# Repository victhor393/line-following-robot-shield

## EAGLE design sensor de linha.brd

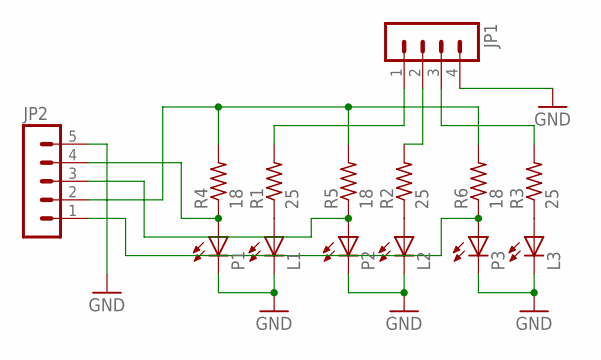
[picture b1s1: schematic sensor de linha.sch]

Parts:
JP1: MA04-1
JP2: MA05-1
L1, L2, L3: LED3MM
P1, P2, P3: LED3MM
R1, R2, R3: 25; R0805
R4, R5, R6: 18; R0805

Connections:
GND: JP1.4, JP2.5, L1.K (C), L2.K (C), L3.K (C), P1.K (C), P2.K (C), P3.K (C)
unnamed: JP1.1, R1.2
unnamed: L1.A, R1.1
unnamed: JP1.2, R2.2
unnamed: JP1.3, R3.2
unnamed: L2.A, R2.1
unnamed: L3.A, R3.1
unnamed: JP2.4, P1.A, R4.1
unnamed: JP2.1, P3.A, R6.1
unnamed: JP2.2, R4.2, R5.2, R6.2
unnamed: JP2.3, P2.A, R5.1

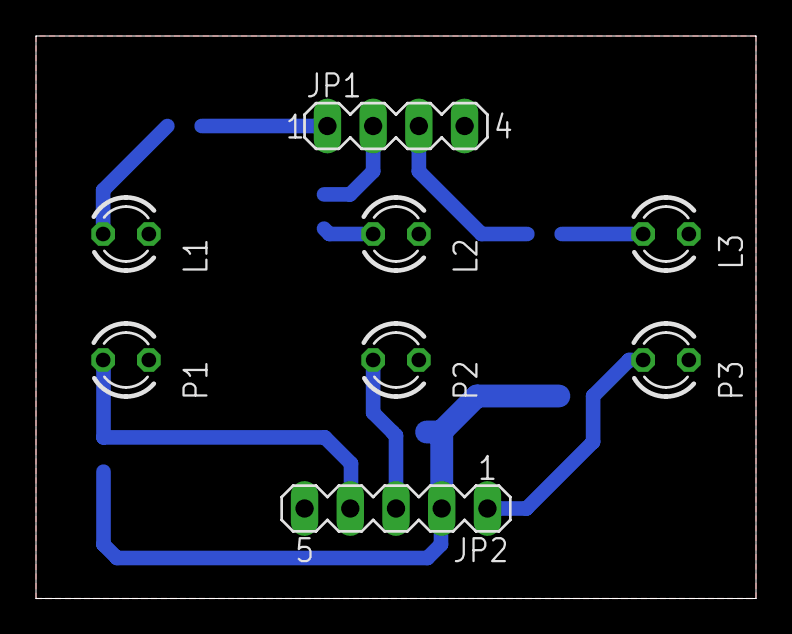
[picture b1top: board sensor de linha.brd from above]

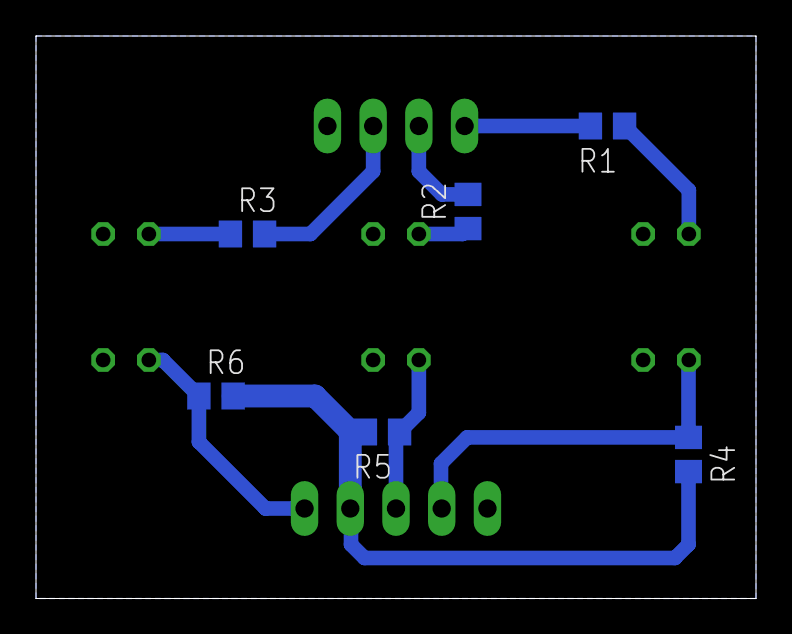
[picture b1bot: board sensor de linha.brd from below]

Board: 2 copper layers, 40.0 x 31.2 mm, 14 parts (6 on the bottom side), 11 nets.

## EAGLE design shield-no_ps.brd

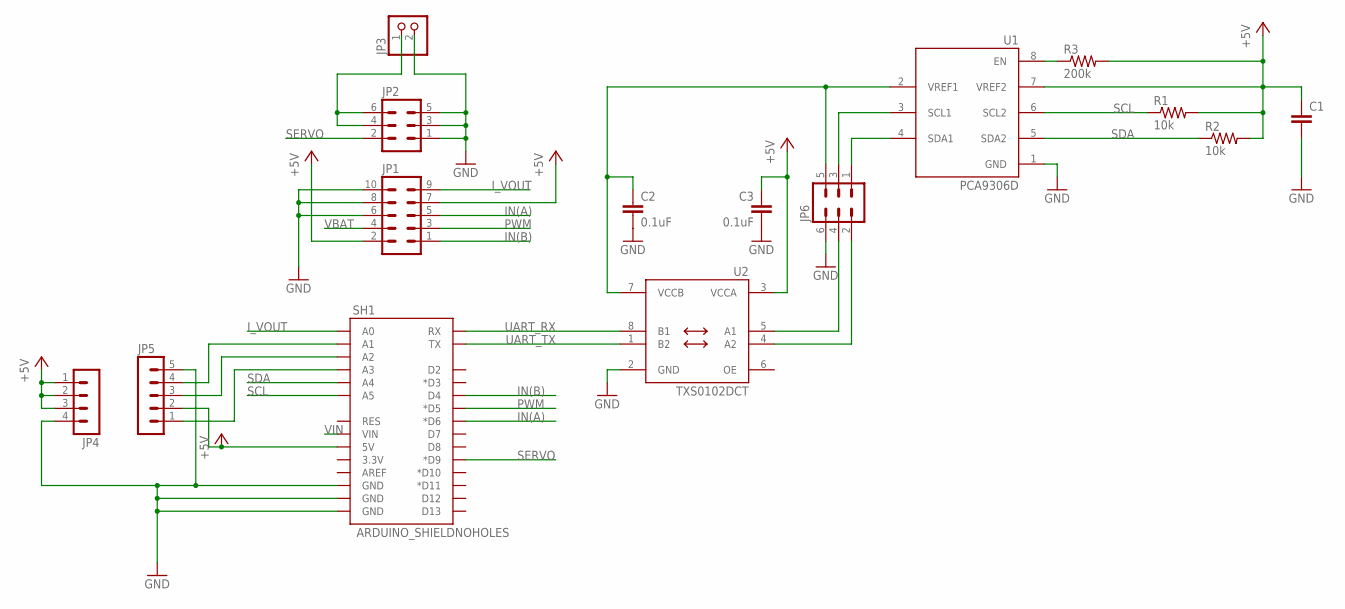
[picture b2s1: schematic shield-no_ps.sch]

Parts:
C1: C-EUC0805; C0805
C2, C3: 0.1uF; C0603
JP1: ML10
JP2, JP6: ML6
JP3: PINHD-1X2; 1X02
JP4: MA04-1
JP5: MA05-1
R1, R2: 10k; R0805
R3: 200k; R0603
SH1: ARDUINO_SHIELDNOHOLES; DUEMILANOVE_SHIELD_NOHOLES
U1: PCA9306D; SO8
U2: TXS0102DCT; DCT_R-PDSO-G8

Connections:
+5V: C1.1, C3.1, JP1.2, JP1.7, JP4.1, JP4.2, JP4.3, JP5.2, R1.2, R2.2, R3.2, SH1.5V, U1.7 (VREF2), U2.3 (VCCA)
GND: C1.2, C2.2, C3.2, JP1.6, JP1.8, JP1.10, JP2.1, JP2.3, JP2.5, JP3.2, JP4.4, JP5.5, JP6.6, SH1.GND@0 (GND), SH1.GND@1 (GND), SH1.GND@2 (GND), U1.1 (GND), U2.2 (GND)
IN(A): JP1.5, SH1.D6 (*D6)
IN(B): JP1.1, SH1.D4
I_VOUT: JP1.9, SH1.A0
unnamed: C2.1, JP6.5, U1.2 (VREF1), U2.7 (VCCB)
unnamed: JP2.4, JP2.6, JP3.1
unnamed: R3.1, U1.8 (EN)
unnamed: JP6.1, U1.4 (SDA1)
unnamed: JP6.3, U1.3 (SCL1)
unnamed: JP5.4, SH1.A1
unnamed: JP5.3, SH1.A2
unnamed: JP5.1, SH1.A3
unnamed: JP6.2, U2.4 (A2)
unnamed: JP6.4, U2.5 (A1)
PWM: JP1.3, SH1.D5 (*D5)
SCL: R1.1, SH1.A5, U1.6 (SCL2)
SDA: R2.1, SH1.A4, U1.5 (SDA2)
SERVO: JP2.2, SH1.D9 (*D9)
UART_RX: SH1.RX, U2.8 (B1)
UART_TX: SH1.TX, U2.1 (B2)
VBAT: JP1.4
VIN: SH1.VIN

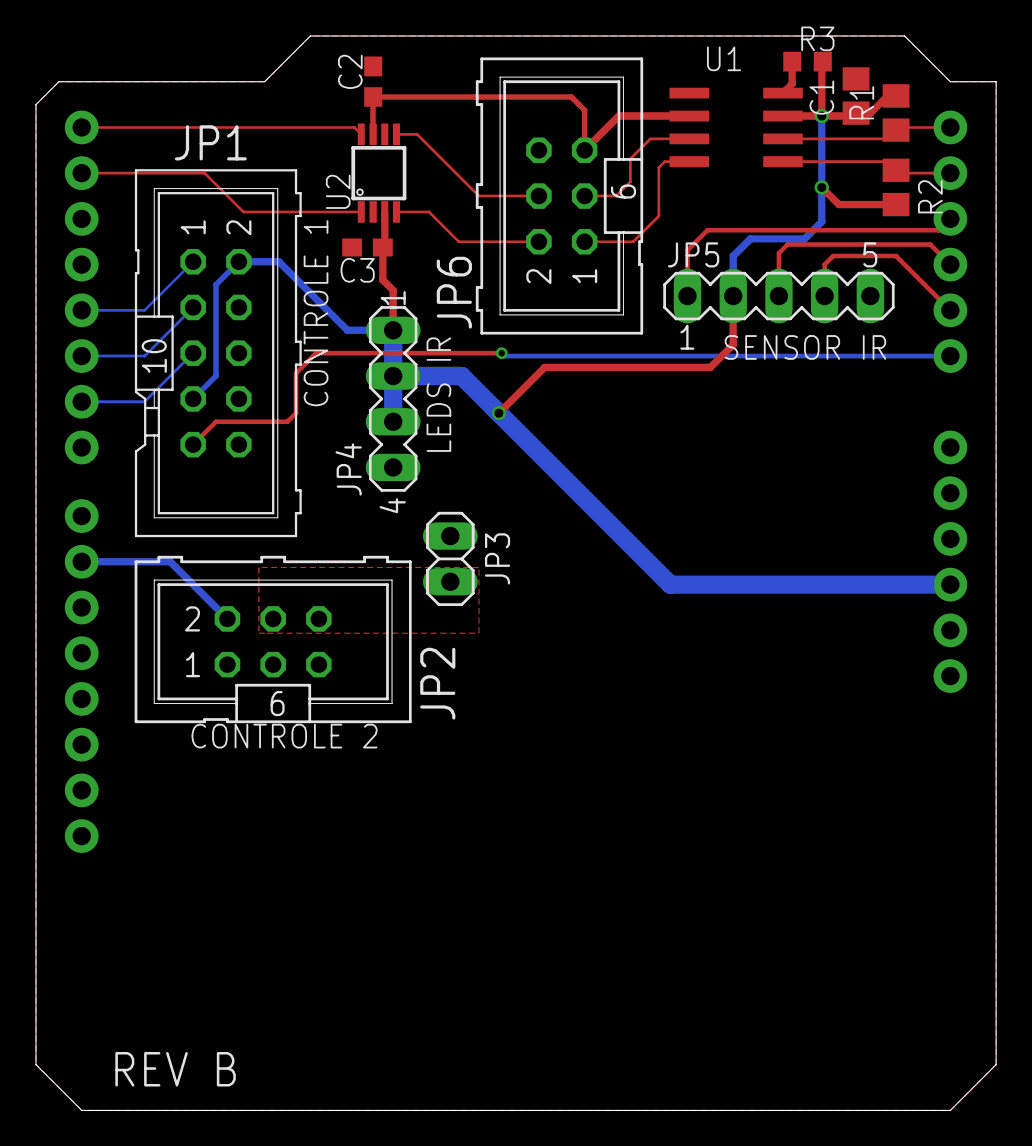
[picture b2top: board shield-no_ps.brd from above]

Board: 2 copper layers, 53.3 x 59.7 mm, 15 parts (0 on the bottom side), 21 nets.

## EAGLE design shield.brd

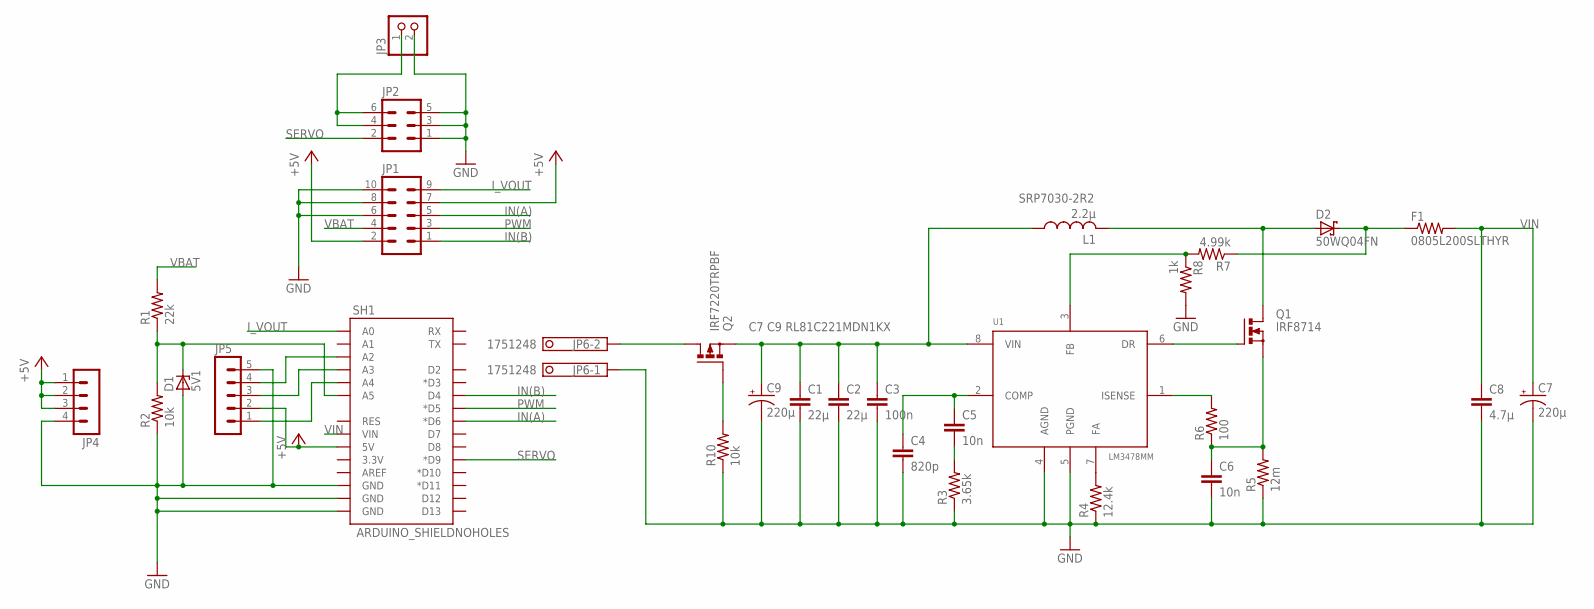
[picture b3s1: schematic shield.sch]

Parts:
C1, C2: 22µ; C3225
C3: 100n; C0805
C4: 820p; C0805
C5, C6: 10n; C0805
C7, C9: 220µ; E3,5-8
C8: 4.7µ; C3225
D1: 5V1; SOT23
D2: 50WQ04FN; DPACK_1
F1: 0805L200SLTHYR; R0805
JP1: ML10
JP2: ML6
JP3: PINHD-1X2; 1X02
JP4: MA04-1
JP5: MA05-1
JP6: 1751248
L1: 2.2µ; SRP7030
Q1: IRF8714; SO-08
Q2: IRF7220TRPBF; SO-08
R1: 22k; R0805
R2, R10: 10k; R0805
R3: 3.65k; R0805
R4: 12.4k; R0805
R5: 12m; R1206
R6: 100; R0805
R7: 4.99k; R0805
R8: 1k; R0805
SH1: ARDUINO_SHIELDNOHOLES; DUEMILANOVE_SHIELD_NOHOLES
U1: LM3478MM; DGK_S-PDSO-G8

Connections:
+5V: JP1.2, JP1.7, JP4.1, JP4.2, JP4.3, JP5.2, SH1.5V
GND: C1.2, C2.2, C3.2, C4.2, C6.2, C7.-, C8.2, C9.-, D1.1 (A), JP1.6, JP1.8, JP1.10, JP2.1, JP2.3, JP2.5, JP3.2, JP4.4, JP5.5, JP6.1, R2.1, R3.1, R4.1, R5.1, R8.2, R10.1, SH1.GND@0 (GND), SH1.GND@1 (GND), SH1.GND@2 (GND), U1.4 (AGND), U1.5 (PGND)
IN(A): JP1.5, SH1.D6 (*D6)
IN(B): JP1.1, SH1.D4
I_VOUT: JP1.9, SH1.A0
unnamed: D1.3 (C), R1.1, R2.2, SH1.A5
unnamed: JP2.4, JP2.6, JP3.1
unnamed: D2.K (C), F1.1, R7.1
unnamed: JP6.2, Q2.5 (D), Q2.6 (D), Q2.7 (D), Q2.8 (D)
unnamed: Q2.4 (G), R10.2
unnamed: JP5.4, SH1.A2
unnamed: JP5.3, SH1.A3
unnamed: JP5.1, SH1.A4
unnamed: R4.2, U1.7 (FA)
unnamed: C5.2, R3.2
unnamed: C4.1, C5.1, U1.2 (COMP)
unnamed: C1.1, C2.1, C3.1, C9.+, L1.1, Q2.1 (S), Q2.2 (S), Q2.3 (S), U1.8 (VIN)
unnamed: Q1.4 (G), U1.6 (DR)
unnamed: C6.1, Q1.1 (S), Q1.2 (S), Q1.3 (S), R5.2, R6.1
unnamed: R6.2, U1.1 (ISENSE)
unnamed: D2.A1 (A), D2.A2 (A), L1.2, Q1.5 (D), Q1.6 (D), Q1.7 (D), Q1.8 (D)
unnamed: R7.2, R8.1, U1.3 (FB)
PWM: JP1.3, SH1.D5 (*D5)
SERVO: JP2.2, SH1.D9 (*D9)
VBAT: JP1.4, R1.2
VIN: C7.+, C8.1, F1.2, SH1.VIN

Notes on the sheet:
SRP7030-2R2
C7 C9 RL81C221MDN1KX

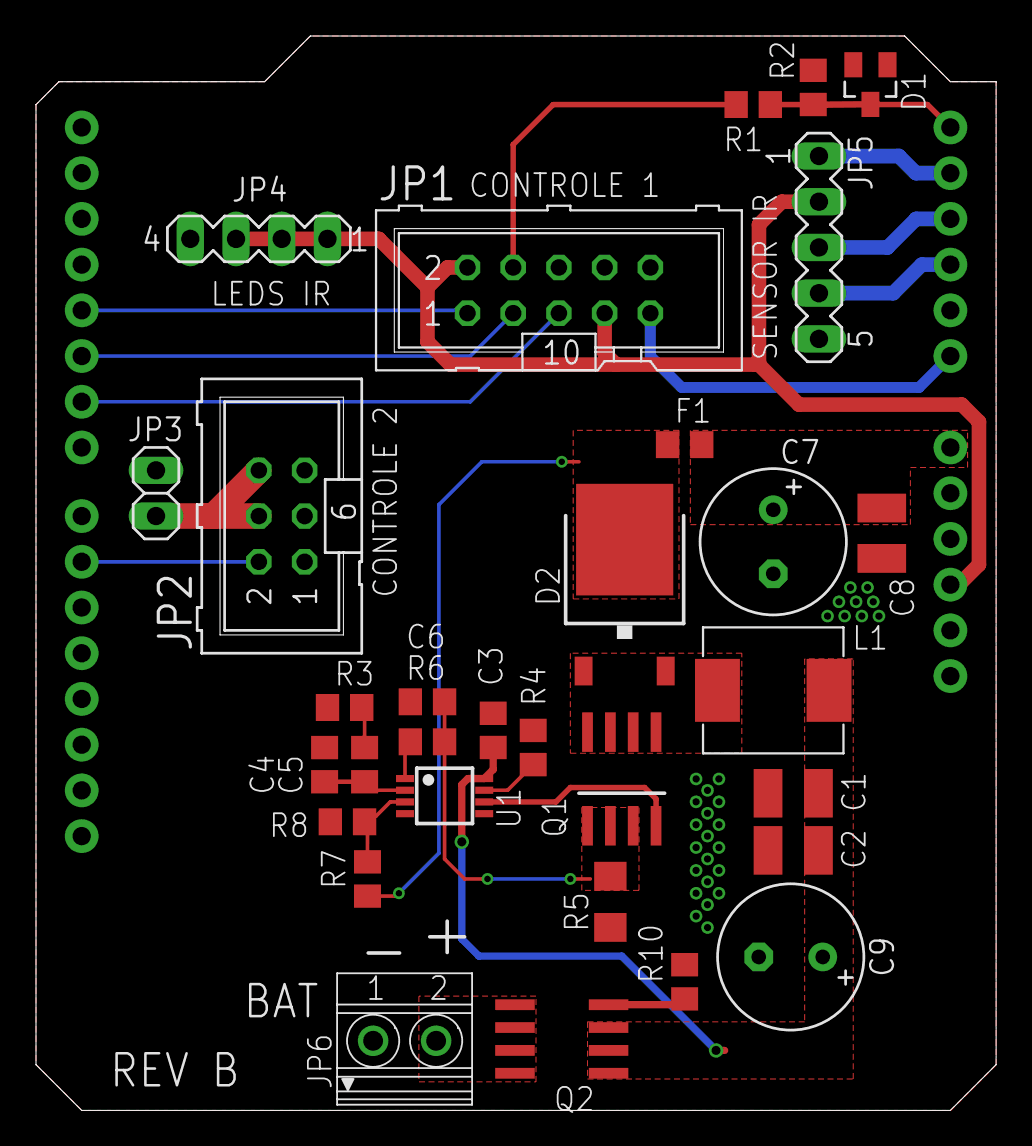
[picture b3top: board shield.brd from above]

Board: 2 copper layers, 53.3 x 59.7 mm, 32 parts (0 on the bottom side), 26 nets.

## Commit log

2019-05-12 Initial commit fix
2019-05-21 Added schematic and board layout in pdf format

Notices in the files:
parts and their libraries:
SparkFun-Boards: Licensing: CC v3.0 Share-Alike You are welcome to use this library for commercial purposes.
